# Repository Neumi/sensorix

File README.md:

# sensorix
Low cost, easy to build machine to human interface. Using electrical skin stimulation to transfer information from machines to human.

## some PCB images

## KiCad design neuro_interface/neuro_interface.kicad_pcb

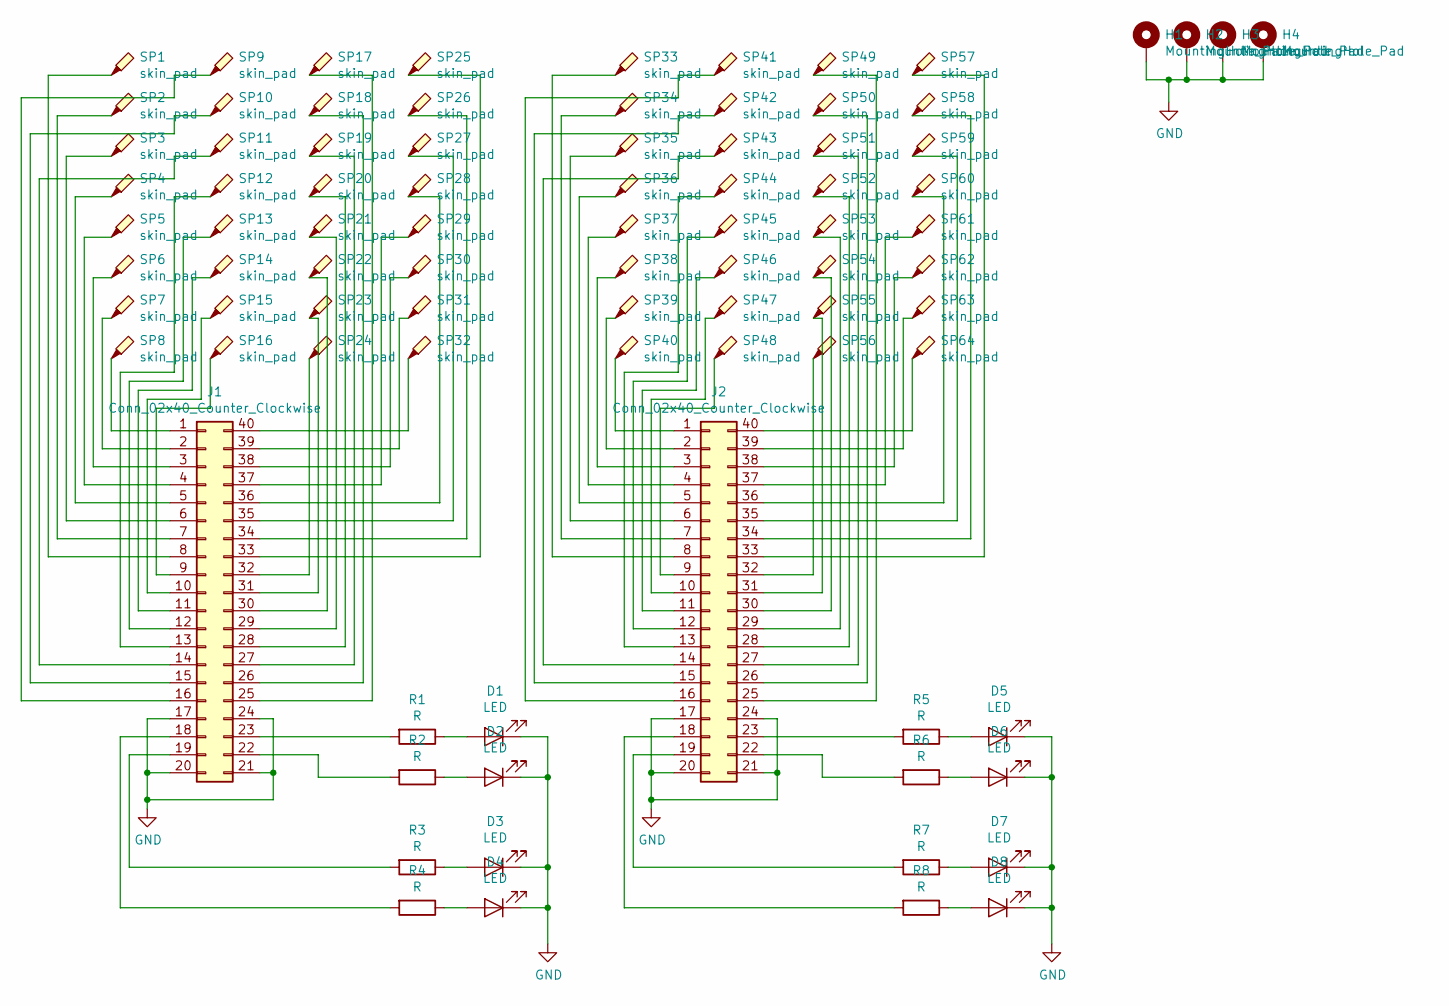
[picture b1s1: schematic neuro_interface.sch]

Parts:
D1, D2, D3, D4, D5, D6, D7, D8: LED; LED_0805_HandSoldering
H1, H2, H3, H4: MountingHole_Pad; MountingHole_3.2mm_M3_Pad_Via
J1, J2: Conn_02x40_Counter_Clockwise; FTS-120-XX-XX-DV
R1, R2, R3, R4, R5, R6, R7, R8: R; R_0805_HandSoldering
SP1, SP2, SP3, SP4, SP5, SP6, SP7, SP8, SP9, SP10, SP11, SP12, SP13, SP14, SP15, SP16, SP17, SP18, SP19, SP20, SP21, SP22, SP23, SP24, SP25, SP26, SP27, SP28, SP29, SP30, SP31, SP32, SP33, SP34, SP35, SP36, SP37, SP38, SP39, SP40, SP41, SP42, SP43, SP44, SP45, SP46, SP47, SP48, SP49, SP50, SP51, SP52, SP53, SP54, SP55, SP56, SP57, SP58, SP59, SP60, SP61, SP62, SP63, SP64: skin_pad; Test_Point_Pad_d3.0mm

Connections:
GND: D1.1 (K), D2.1 (K), D3.1 (K), D4.1 (K), D5.1 (K), D6.1 (K), D7.1 (K), D8.1 (K), H1.1, H2.1, H3.1, H4.1, J1.17, J1.20, J1.21, J1.24, J2.17, J2.20, J2.21, J2.24
unnamed: D1.2 (A), R1.1
unnamed: D2.2 (A), R2.1
unnamed: D3.2 (A), R3.1
unnamed: D4.2 (A), R4.1
unnamed: D5.2 (A), R5.1
unnamed: D6.2 (A), R6.1
unnamed: D7.2 (A), R7.1
unnamed: D8.2 (A), R8.1
unnamed: J1.1, SP8.1
unnamed: J1.2, SP7.1
unnamed: J1.3, SP6.1
unnamed: J1.4, SP5.1
unnamed: J1.5, SP4.1
unnamed: J1.6, SP3.1
unnamed: J1.7, SP2.1
unnamed: J1.8, SP1.1
unnamed: J1.9, SP16.1
unnamed: J1.10, SP15.1
unnamed: J1.11, SP14.1
unnamed: J1.12, SP13.1
unnamed: J1.13, SP12.1
unnamed: J1.14, SP11.1
unnamed: J1.15, SP10.1
unnamed: J1.16, SP9.1
unnamed: J1.18, R4.2
unnamed: J1.19, R3.2
unnamed: J1.22, R2.2
unnamed: J1.23, R1.2
unnamed: J1.25, SP17.1
unnamed: J1.26, SP18.1
unnamed: J1.27, SP19.1
unnamed: J1.28, SP20.1
unnamed: J1.29, SP21.1
unnamed: J1.30, SP22.1
unnamed: J1.31, SP23.1
unnamed: J1.32, SP24.1
unnamed: J1.33, SP25.1
unnamed: J1.34, SP26.1
unnamed: J1.35, SP27.1
unnamed: J1.36, SP28.1
unnamed: J1.37, SP29.1
unnamed: J1.38, SP30.1
unnamed: J1.39, SP31.1
unnamed: J1.40, SP32.1
unnamed: J2.1, SP40.1
unnamed: J2.2, SP39.1
unnamed: J2.3, SP38.1
unnamed: J2.4, SP37.1
unnamed: J2.5, SP36.1
unnamed: J2.6, SP35.1
unnamed: J2.7, SP34.1
unnamed: J2.8, SP33.1
unnamed: J2.9, SP48.1
unnamed: J2.10, SP47.1
unnamed: J2.11, SP46.1
unnamed: J2.12, SP45.1
unnamed: J2.13, SP44.1
unnamed: J2.14, SP43.1
unnamed: J2.15, SP42.1
unnamed: J2.16, SP41.1
unnamed: J2.18, R8.2
unnamed: J2.19, R7.2
unnamed: J2.22, R6.2
unnamed: J2.23, R5.2
unnamed: J2.25, SP49.1
unnamed: J2.26, SP50.1
unnamed: J2.27, SP51.1
unnamed: J2.28, SP52.1
unnamed: J2.29, SP53.1
unnamed: J2.30, SP54.1
unnamed: J2.31, SP55.1
unnamed: J2.32, SP56.1
unnamed: J2.33, SP57.1
unnamed: J2.34, SP58.1
unnamed: J2.35, SP59.1
unnamed: J2.36, SP60.1
unnamed: J2.37, SP61.1
unnamed: J2.38, SP62.1
unnamed: J2.39, SP63.1
unnamed: J2.40, SP64.1

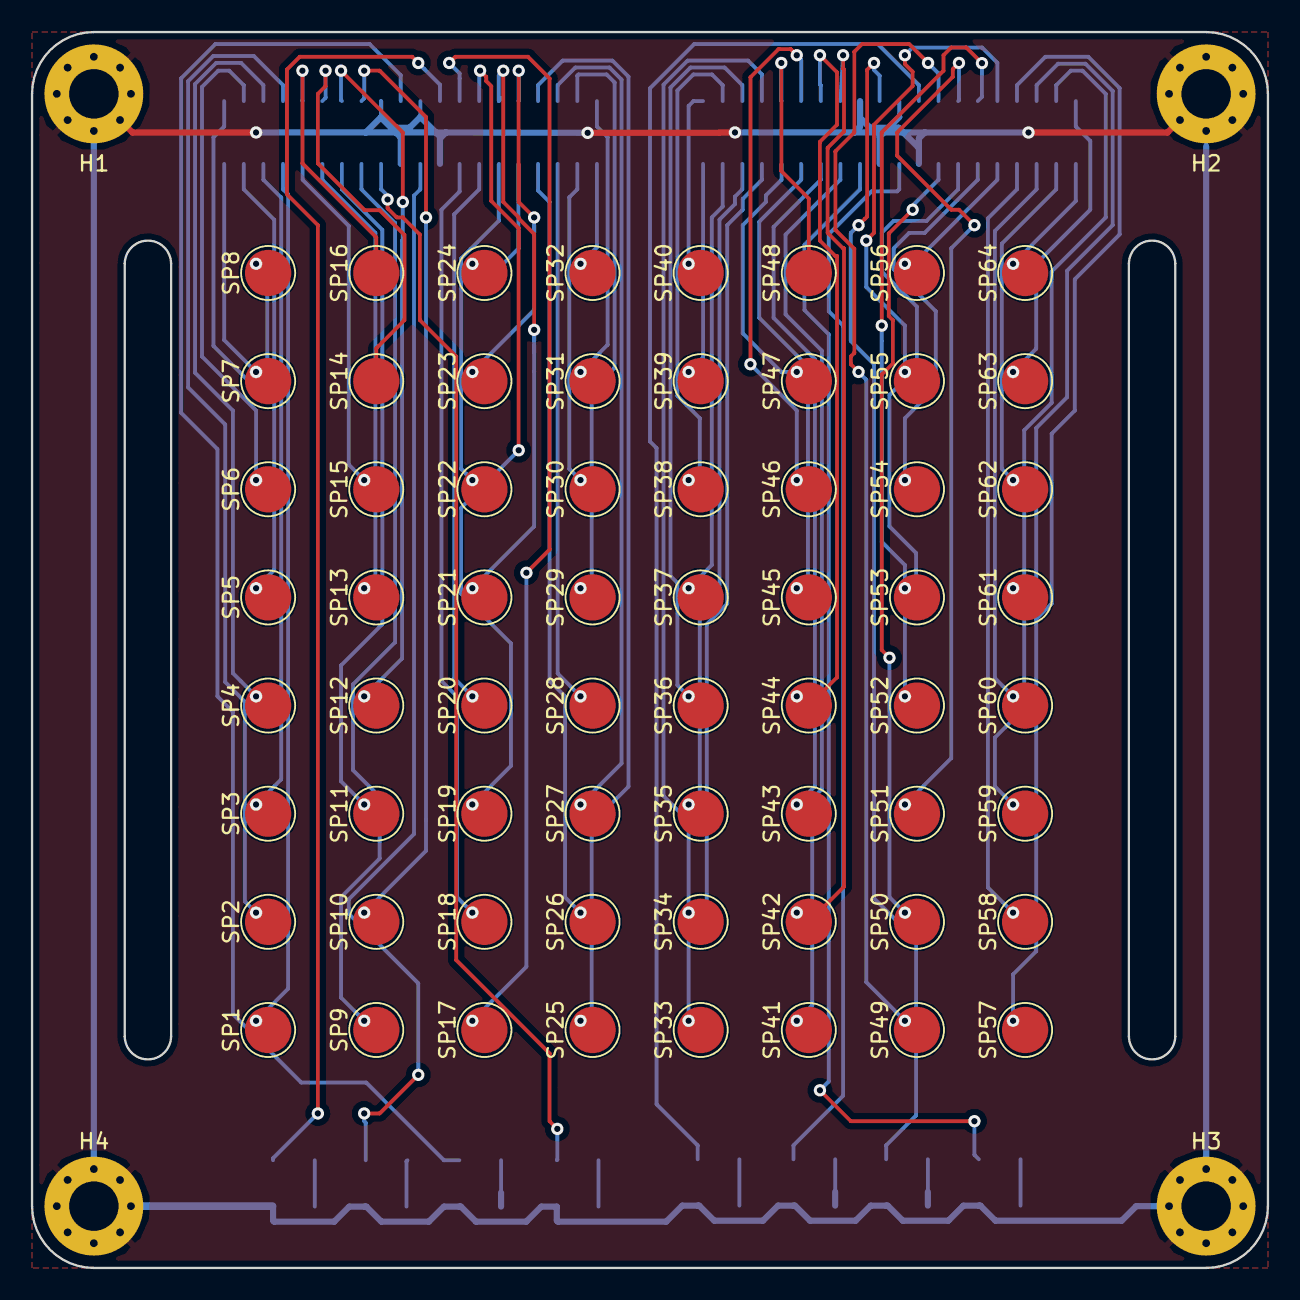
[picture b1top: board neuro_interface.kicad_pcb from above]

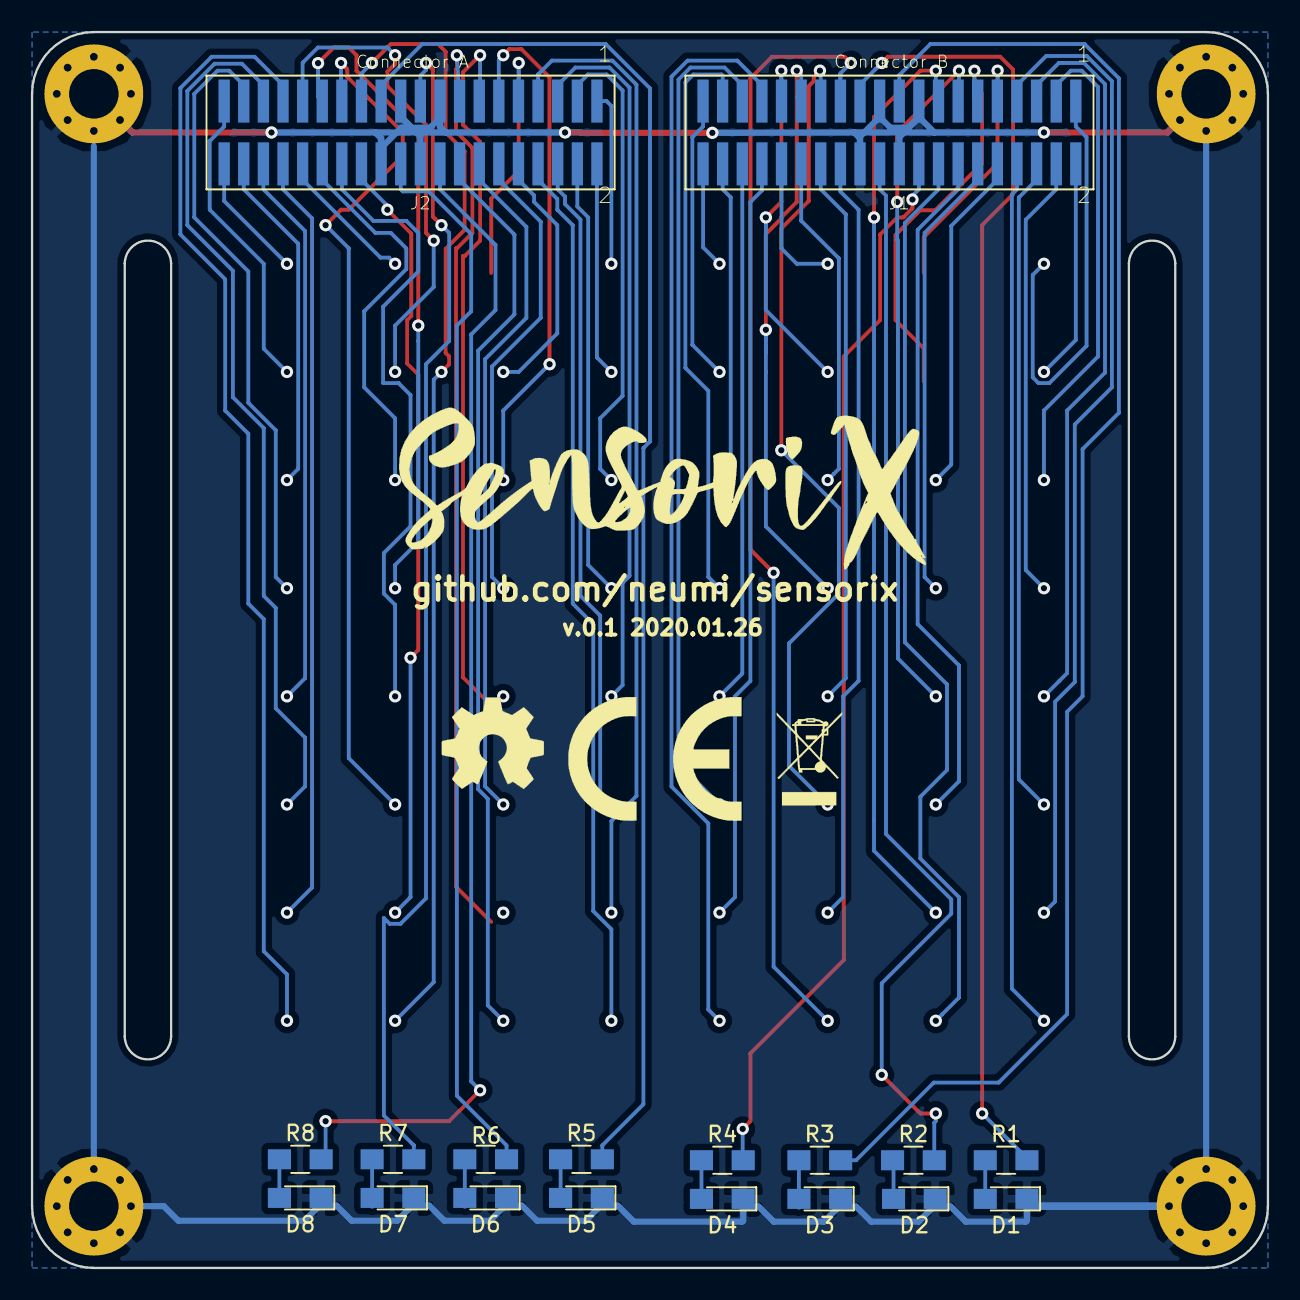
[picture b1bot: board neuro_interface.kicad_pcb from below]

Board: 2 copper layers, 80.0 x 80.0 mm, 86 parts (18 on the bottom side), 81 nets.

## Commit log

2019-12-14 added interface board and interface board images
2019-12-17 fixed overlap
2020-01-26 added ground plane on non-skin side
